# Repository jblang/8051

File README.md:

# 8051 Board for RC2014

This is a board design for an 8051 (specifically, for the Maxim DS80C320). I had the board manufactured but initial bringup was not successful, and I have not had time to debug it.  I am posting on GitHub as a backup in case I ever get back to it, or in case anyone else wants to take it further.

## License

Copyright 2021 J.B. Langston

Permission is hereby granted, free of charge, to any person obtaining a copy of this software and associated documentation files (the "Software"), to deal in the Software without restriction, including without limitation the rights to use, copy, modify, merge, publish, distribute, sublicense, and/or sell copies of the Software, and to permit persons to whom the Software is furnished to do so, subject to the following conditions:

The above copyright notice and this permission notice shall be included in all copies or substantial portions of the Software.

THE SOFTWARE IS PROVIDED "AS IS", WITHOUT WARRANTY OF ANY KIND, EXPRESS OR IMPLIED, INCLUDING BUT NOT LIMITED TO THE WARRANTIES OF MERCHANTABILITY, FITNESS FOR A PARTICULAR PURPOSE AND NONINFRINGEMENT. IN NO EVENT SHALL THE AUTHORS OR COPYRIGHT HOLDERS BE LIABLE FOR ANY CLAIM, DAMAGES OR OTHER LIABILITY, WHETHER IN AN ACTION OF CONTRACT, TORT OR OTHERWISE, ARISING FROM, OUT OF OR IN CONNECTION WITH THE SOFTWARE OR THE USE OR OTHER DEALINGS IN THE SOFTWARE.

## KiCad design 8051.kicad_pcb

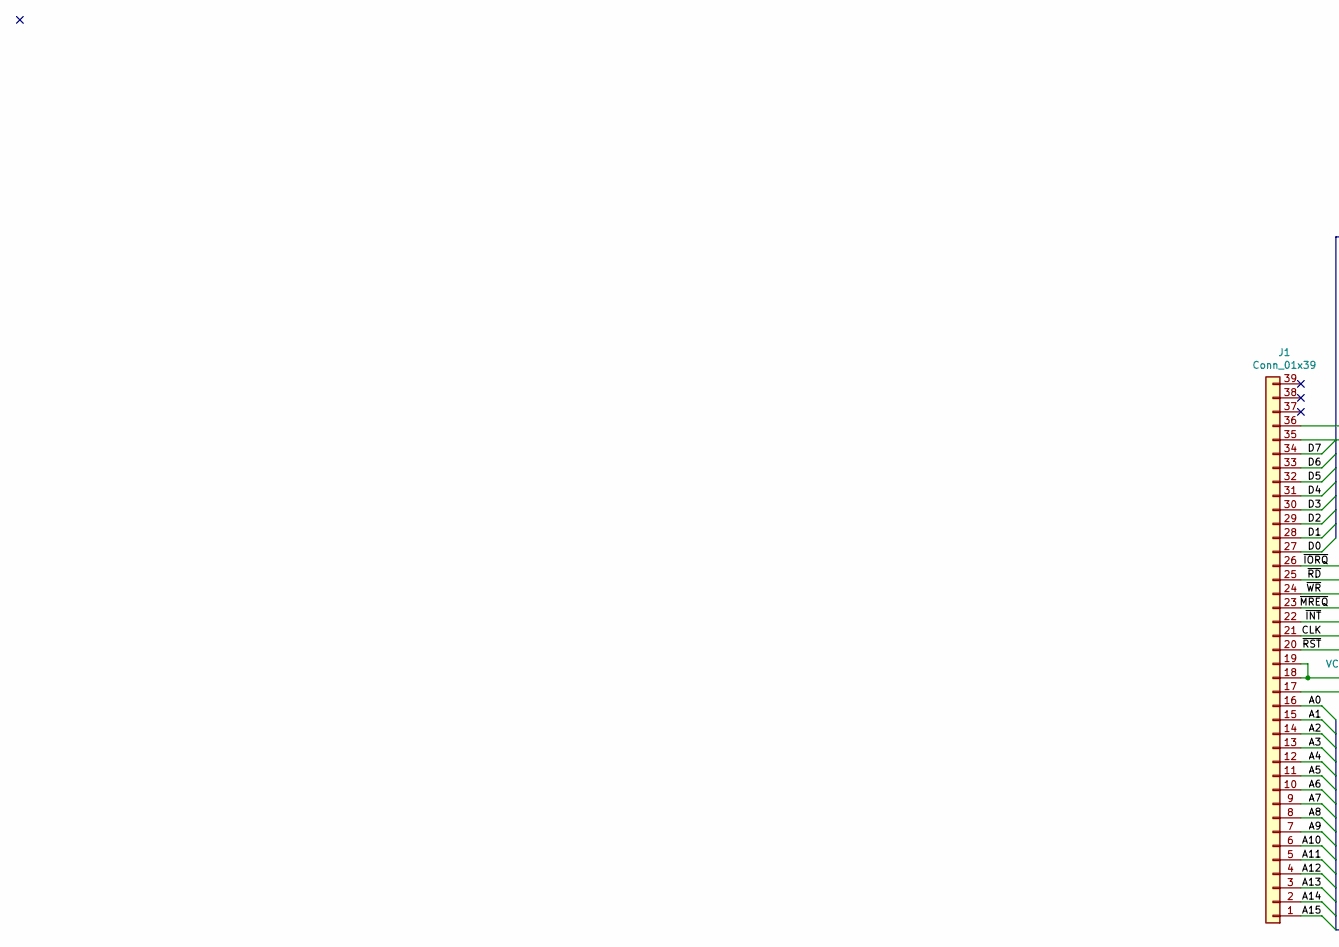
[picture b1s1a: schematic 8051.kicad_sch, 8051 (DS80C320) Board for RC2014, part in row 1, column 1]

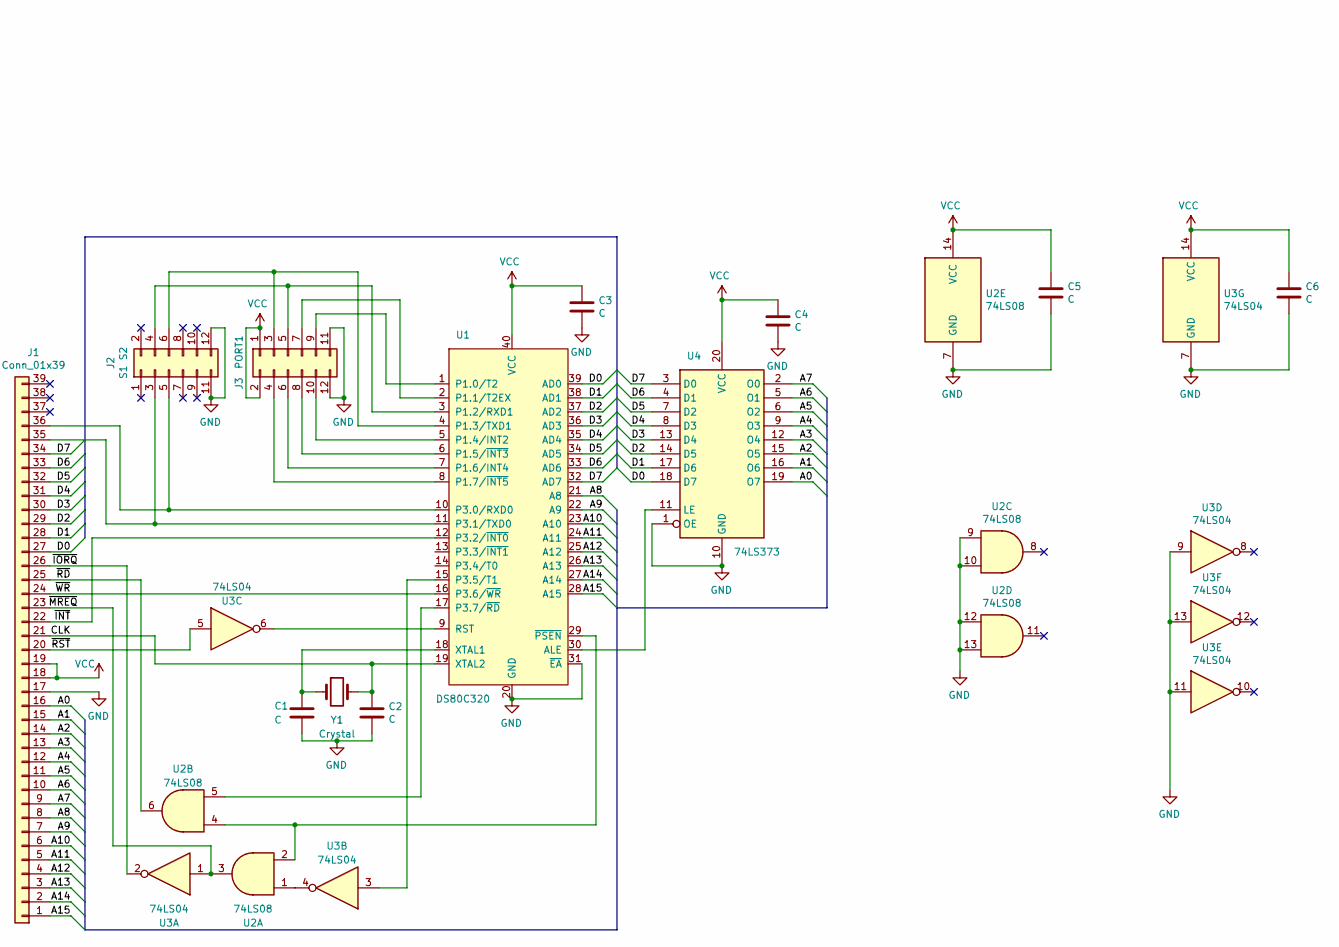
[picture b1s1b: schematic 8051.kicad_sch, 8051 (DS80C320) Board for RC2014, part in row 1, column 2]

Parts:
C1, C2, C3, C4, C5, C6: C; C_Disc_D3.0mm_W1.6mm_P2.50mm
J1: Conn_01x39; PinHeader_1x39_P2.54mm_Vertical
J2: S1 S2; PinHeader_2x06_P2.54mm_Horizontal
J3: PORT1; PinSocket_2x06_P2.54mm_Vertical
U1: DS80C320; DIP-40_W15.24mm
U2: 74LS08; DIP-14_W7.62mm
U3: 74LS04; DIP-14_W7.62mm
U4: 74LS373; DIP-20_W7.62mm
Y1: Crystal; Crystal_HC49-4H_Vertical

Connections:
/A0: J1.16, U4.19 (O7)
/A1: J1.15, U4.16 (O6)
/A2: J1.14, U4.15 (O5)
/A3: J1.13, U4.12 (O4)
/A4: J1.12, U4.9 (O3)
/A5: J1.11, U4.6 (O2)
/A6: J1.10, U4.5 (O1)
/A7: J1.9, U4.2 (O0)
/A8: J1.8, U1.21 (A8)
/A9: J1.7, U1.22 (A9)
/A10: J1.6, U1.23 (A10)
/A11: J1.5, U1.24 (A11)
/A12: J1.4, U1.25 (A12)
/A13: J1.3, U1.26 (A13)
/A14: J1.2, U1.27 (A14)
/A15: J1.1, U1.28 (A15)
/CLK: C2.1, J1.21, U1.19 (XTAL2), Y1.2
/D0: J1.27, U1.39 (AD0), U4.18 (D7)
/D1: J1.28, U1.38 (AD1), U4.17 (D6)
/D2: J1.29, U1.37 (AD2), U4.14 (D5)
/D3: J1.30, U1.36 (AD3), U4.13 (D4)
/D4: J1.31, U1.35 (AD4), U4.8 (D3)
/D5: J1.32, U1.34 (AD5), U4.7 (D2)
/D6: J1.33, U1.33 (AD6), U4.4 (D1)
/D7: J1.34, U1.32 (AD7), U4.3 (D0)
/~INT: J1.22, U1.12 (P3.2/~INT0)
/~IORQ: J1.26, U3.2
/~MREQ: J1.23, U2.3, U3.1
/~RD: J1.25, U2.6
/~RST: J1.20, U3.5
/~WR: J1.24, U1.16 (P3.6/~WR)
GND: C1.2, C2.2, C3.2, C4.2, C5.2, C6.2, J1.17, J2.11, J2.12, J3.11, J3.12, U1.20 (GND), U1.31 (~EA), U2.7 (GND), U2.9, U2.10, U2.12, U2.13, U3.7 (GND), U3.9, U3.11, U3.13, U4.1 (OE), U4.10 (GND)
unnamed: C1.1, U1.18 (XTAL1), Y1.1
unnamed: J1.35, J2.3, U1.11 (P3.1/TXD0)
unnamed: J1.36, J2.5, U1.10 (P3.0/RXD0)
unnamed: J2.4, J3.5, U1.3 (P1.2/RXD1)
unnamed: J2.6, J3.3, U1.4 (P1.3/TXD1)
unnamed: J3.4, U1.8 (P1.7/~INT5)
unnamed: J3.6, U1.7 (P1.6/INT4)
unnamed: J3.7, U1.2 (P1.1/T2EX)
unnamed: J3.8, U1.6 (P1.5/~INT3)
unnamed: J3.9, U1.1 (P1.0/T2)
unnamed: J3.10, U1.5 (P1.4/INT2)
unnamed: U1.9 (RST), U3.6
unnamed: U1.15 (P3.5/T1), U3.3
unnamed: U1.17 (P3.7/~RD), U2.5
unnamed: U1.29 (~PSEN), U2.2, U2.4
unnamed: U1.30 (ALE), U4.11 (LE)
unnamed: U2.1, U3.4
VCC: C3.1, C4.1, C5.1, C6.1, J1.18, J1.19, J3.1, J3.2, U1.40 (VCC), U2.14 (VCC), U3.14 (VCC), U4.20 (VCC)

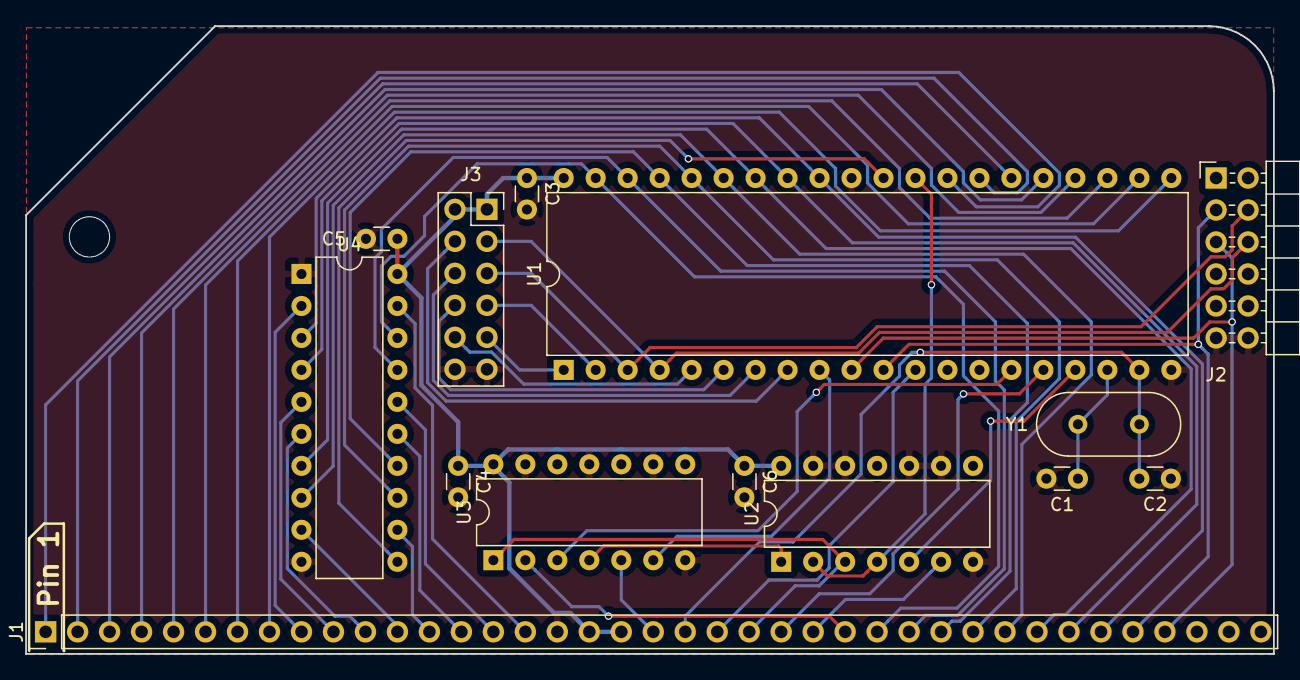
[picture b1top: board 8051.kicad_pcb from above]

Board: 2 copper layers, 99.1 x 49.9 mm, 14 parts (0 on the bottom side), 50 nets.

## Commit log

2022-10-22 Upgrade Kicad projects to v6
